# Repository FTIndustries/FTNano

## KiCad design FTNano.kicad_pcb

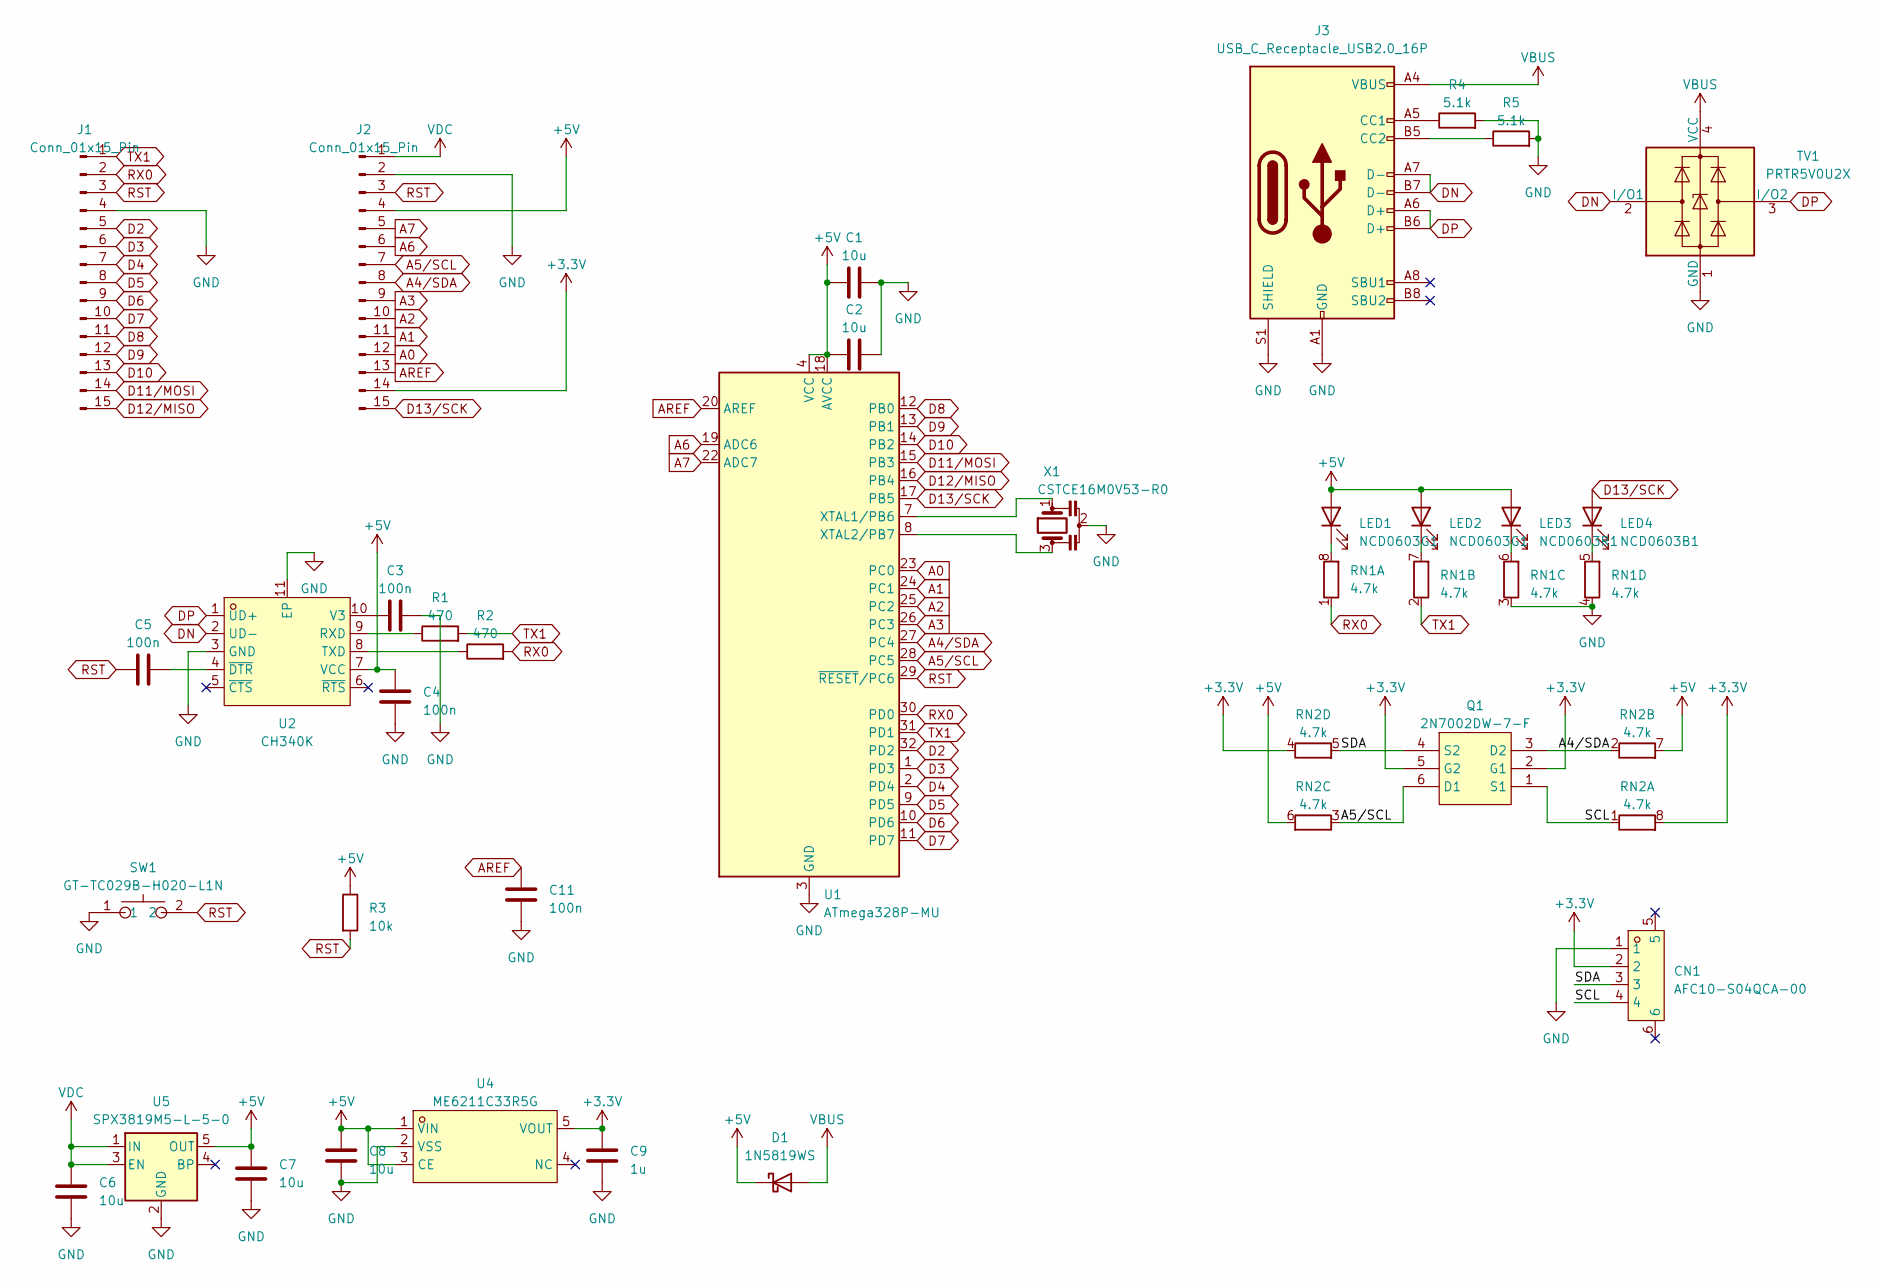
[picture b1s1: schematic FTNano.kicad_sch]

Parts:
C1, C2, C6, C7, C8: 10u; C_0603_1608Metric
C3, C4, C5, C11: 100n; C_0402_1005Metric
C9: 1u; C_0603_1608Metric
CN1: AFC10-S04QCA-00; CONN-SMD_AFC10-S04QCA-00; LCSC Part C2764183
D1: 1N5819WS; D_SOD-323
J1, J2: Conn_01x15_Pin; PinHeader_1x15_P2.54mm_Vertical
J3: USB_C_Receptacle_USB2.0_16P; USB_C_Receptacle_G-Switch_GT-USB-7010ASV
LED1, LED2: NCD0603G1; LED_0603_1608Metric
LED3: NCD0603R1; LED_0603_1608Metric
LED4: NCD0603B1; LED_0603_1608Metric
Q1: 2N7002DW-7-F; SOT-363_L2.0-W1.3-P0.65-LS2.1-TL; LCSC Part C83571
R1, R2: 470; R_0402_1005Metric
R3: 10k; R_0402_1005Metric
R4, R5: 5.1k; R_0402_1005Metric
RN1, RN2: 4.7k; R_Array_Concave_4x0402
SW1: GT-TC029B-H020-L1N; SW-SMD_L3.9-W2.9-P4.15-LS5.0; LCSC Part C843665
TV1: PRTR5V0U2X; SOT-143
U1: ATmega328P-MU; QFN-32-1EP_5x5mm_P0.5mm_EP3.1x3.1mm
U2: CH340K; ESOP-10_L4.9-W3.9-P1.00-LS6.2-BL-EP; LCSC Part C968586
U4: ME6211C33R5G; SOT-353_L2.1-W1.3-P0.65-LS2.3-BL; LCSC Part C235316
U5: SPX3819M5-L-5-0; SOT-23-5
X1: CSTCE16M0V53-R0; OSC-SMD_3P-L3.2-W1.3-P0.95-L; LCSC Part C32180

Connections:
+3.3V: C9.2, CN1.2, J2.14, Q1.2 (G1), Q1.5 (G2), RN2.4 (R4.1), RN2.8 (R1.2), U4.5 (VOUT)
+5V: C1.1, C2.1, C4.2, C7.2, C8.2, D1.1 (K), J2.4, LED1.2 (A), LED2.2 (A), LED3.2 (A), R3.1, RN2.6 (R3.2), RN2.7 (R2.2), U1.4 (VCC), U1.6 (VCC), U1.18 (AVCC), U2.7 (VCC), U4.1 (VIN), U4.3 (CE), U5.5 (OUT)
/SCL: CN1.4, Q1.1 (S1), RN2.1 (R1.1)
/SDA: CN1.3, Q1.4 (S2), RN2.5 (R4.2)
A0: J2.12, U1.23 (PC0)
A1: J2.11, U1.24 (PC1)
A2: J2.10, U1.25 (PC2)
A3: J2.9, U1.26 (PC3)
A4/SDA: J2.8, Q1.3 (D2), RN2.2 (R2.1), U1.27 (PC4)
A5/SCL: J2.7, Q1.6 (D1), RN2.3 (R3.1), U1.28 (PC5)
A6: J2.6, U1.19 (ADC6)
A7: J2.5, U1.22 (ADC7)
AREF: C11.1, J2.13, U1.20 (AREF)
D2: J1.5, U1.32 (PD2)
D3: J1.6, U1.1 (PD3)
D4: J1.7, U1.2 (PD4)
D5: J1.8, U1.9 (PD5)
D6: J1.9, U1.10 (PD6)
D7: J1.10, U1.11 (PD7)
D8: J1.11, U1.12 (PB0)
D9: J1.12, U1.13 (PB1)
D10: J1.13, U1.14 (PB2)
D11/MOSI: J1.14, U1.15 (PB3)
D12/MISO: J1.15, U1.16 (PB4)
D13/SCK: J2.15, LED4.2 (A), U1.17 (PB5)
DN: J3.A7 (D-), J3.B7 (D-), TV1.2 (I/O1), U2.2 (UD-)
DP: J3.A6 (D+), J3.B6 (D+), TV1.3 (I/O2), U2.1 (UD+)
GND: C1.2, C2.2, C3.2, C4.1, C6.1, C7.1, C8.1, C9.1, C11.2, CN1.1, J1.4, J2.2, J3.A1 (GND), J3.A12 (GND), J3.B1 (GND), J3.B12 (GND), J3.S1 (SHIELD), R4.2, R5.2, RN1.3 (R3.1), RN1.4 (R4.1), SW1.1, TV1.1 (GND), U1.3 (GND), U1.5 (GND), U1.21 (GND), U1.33 (GND), U2.3 (GND), U2.11 (EP), U4.2 (VSS), U5.2 (GND), X1.2
unnamed: J3.A5 (CC1), R4.1
unnamed: J3.B5 (CC2), R5.1
unnamed: LED1.1 (K), RN1.8 (R1.2)
unnamed: LED2.1 (K), RN1.7 (R2.2)
unnamed: LED3.1 (K), RN1.6 (R3.2)
unnamed: LED4.1 (K), RN1.5 (R4.2)
unnamed: U1.7 (XTAL1/PB6), X1.1
unnamed: U1.8 (XTAL2/PB7), X1.3
unnamed: R1.1, U2.9 (RXD)
unnamed: R2.1, U2.8 (TXD)
unnamed: C3.1, U2.10 (V3)
unnamed: C5.2, U2.4 (~DTR)
RST: C5.1, J1.3, J2.3, R3.2, SW1.2, U1.29 (~RESET/PC6)
RX0: J1.2, R2.2, RN1.1 (R1.1), U1.30 (PD0)
TX1: J1.1, R1.2, RN1.2 (R2.1), U1.31 (PD1)
VBUS: D1.2 (A), J3.A4 (VBUS), J3.A9 (VBUS), J3.B4 (VBUS), J3.B9 (VBUS), TV1.4 (VCC)
VDC: C6.2, J2.1, U5.1 (IN), U5.3 (EN)

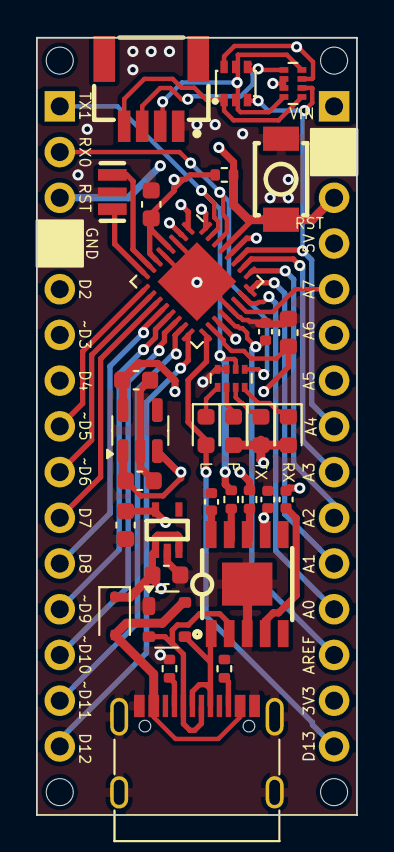
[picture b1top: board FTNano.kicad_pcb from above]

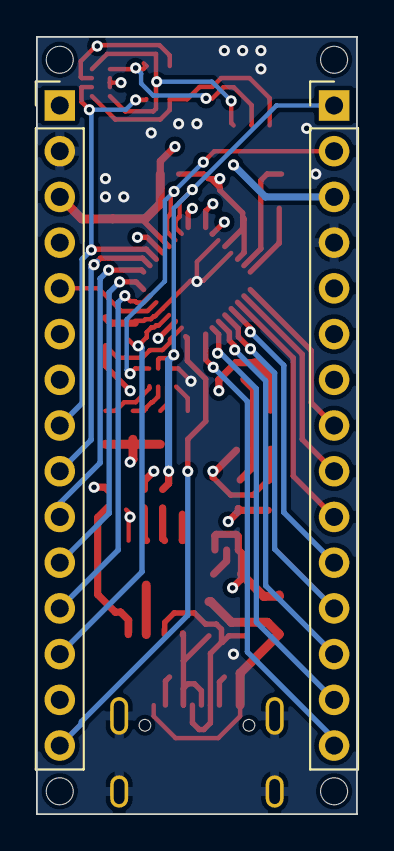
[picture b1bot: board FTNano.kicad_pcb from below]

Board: 4 copper layers, 17.8 x 43.2 mm, 38 parts (2 on the bottom side), 45 nets.

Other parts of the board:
hole1, hole2, hole3, hole4: MountingHole_2.1mm

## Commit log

2024-01-27 ASDF
2024-04-17 fix qwiic, add tvs
2024-05-10 gitignore
2024-06-09 fix led
